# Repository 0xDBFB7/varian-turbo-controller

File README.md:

This is a small, simple half-bridge circuit that commutates 54 volts into 3-phase at 850 Hz, peak power of about 1 kw for a few minutes, for use with the Varian Turbo-V series of turbomolecular pumps. 

> WARNING: This board has only been tested for a few hours. The software does not provide any of the sensing or safety features present in the stock controller. It might blow up your pump, kill your cat, spin the earth around your impeller, etc.
>
> Not that I'm a paragon of best practice in any case, but this seriously isn't an acceptable level of quality. In particular, it was designed to be etched at home, as my normal board house was closed for the holidays.
> I've had one instance where shoot-through blew up one of the MOSFETs. I don't know what would happen if this occurs while the pump is at maximum speed. Adding fuseholders between the legs of the half-bridge - and perhaps between each phase to the pump - would probably be a good idea to prevent catastrophic braking.

There are several other open-source turbomolecular pump controller projects online that are better developed and that might be preferable. In addition, the pumps use a kind of synchronous or induction motor, not a "brushless"-like, so no sensing is needed, only a constant 850 Hz, which is basically just a 3-phase VFD or motor controller. Unfortunately, I wasn't able to find any off-the-shelf system with the required parameters.

The circuit is simple enough to easily be built on perfboard. Schematic and bill of materials are [here](files/controller/assembly). The power MOSFETs are BUK9620, with MIC4604YM-TR half-bridge charge-pump drivers.

The input power was supplied by a MeanWell SE-1000-48 with the voltage trimpot adjusted to ~56V, through a DROK Model 200310 10-75V to 0-60V switching buck converter (Amazon), current limit set to about 8A. 

I highly recommend using such a constant-current regulator, because the power supply is extremely powerful - it's practically an arc flash hazard and will easily start a fire.

The MeanWell supply is probably overkill (very expensive), but a cheaper Amazon 48V supply exploded and I didn't want to tempt fate.

I don't know what terminations the turbopump connector uses; crimp butt connectors worked brilliantly.

## [Original Varian controller manual](references/Varian_V200_controller.pdf)

## [Pump manual](references/Varian_V200_turbo_pump.pdf)

### Things that should be added:

If the back-emf sensing is commutated improperly, -5v or so will be put into the sense ADC pins. The integral protection diodes might be okay with that, but probably not. This is disabled at the moment.

More filtering and decoupling should be added. This pump draws nearly 700 watts on startup - there are some massive transients on the power supply rail.

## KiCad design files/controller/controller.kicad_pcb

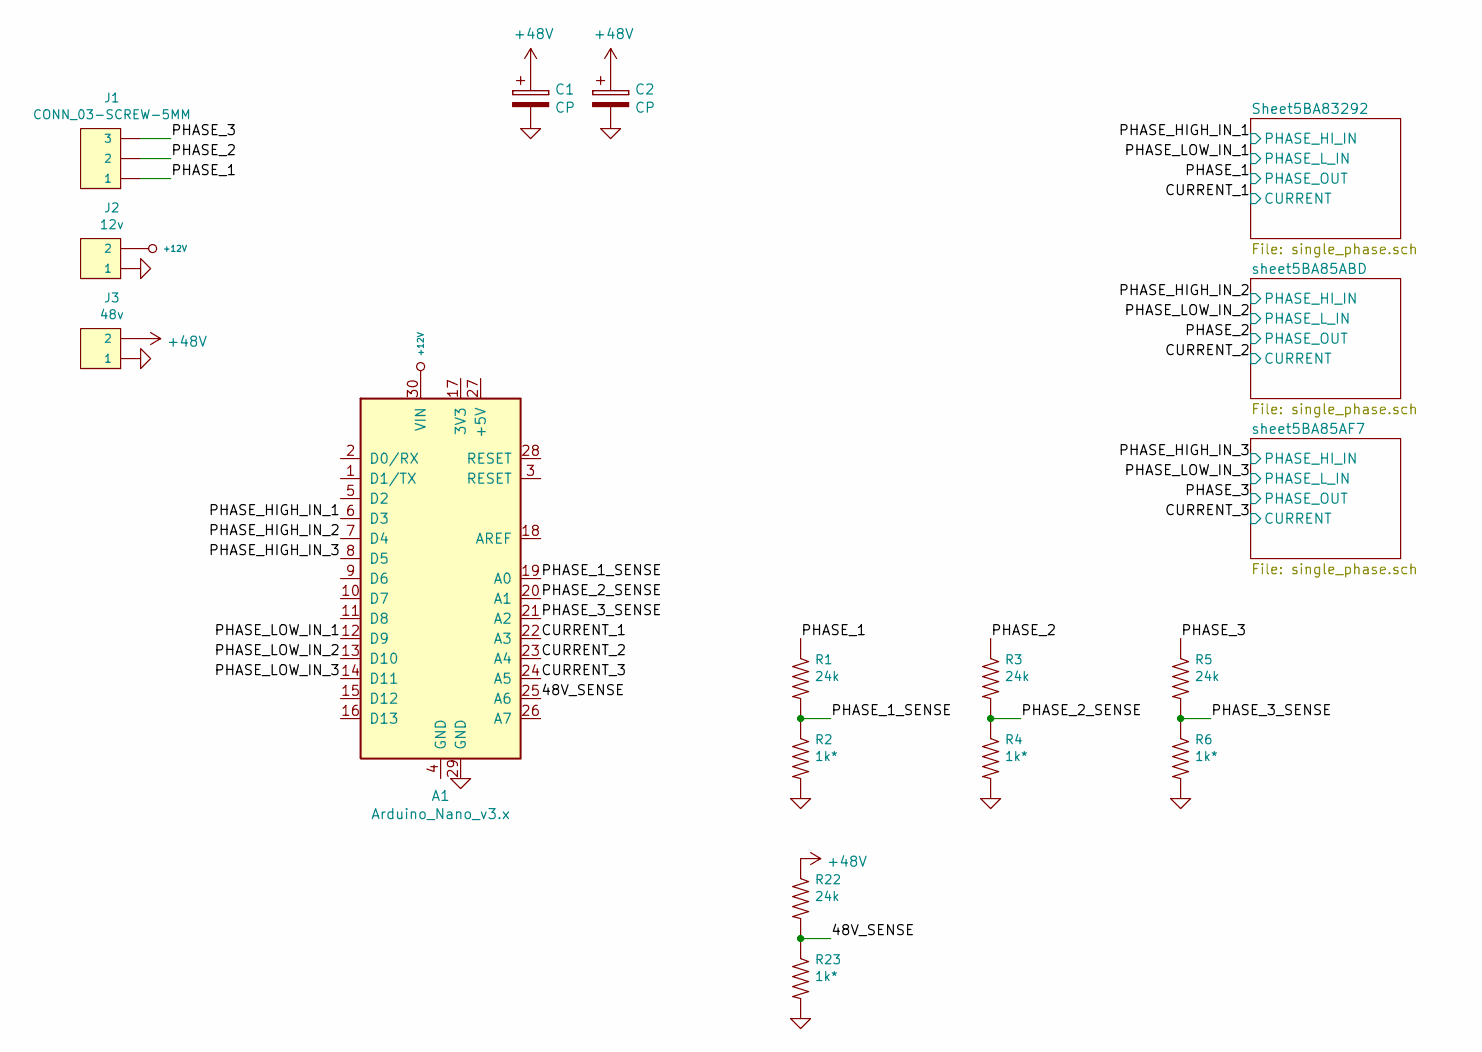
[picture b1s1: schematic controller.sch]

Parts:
A1: Arduino_Nano_v3.x; Arduino_Nano
C1, C2: CP; CP_Radial_D16.0mm_P7.50mm
J1: CONN_03-SCREW-5MM; SCREWTERMINAL-5MM-3
J2: 12v; SCREWTERMINAL-5MM-2
J3: 48v; SCREWTERMINAL-5MM-2
R1, R3, R5, R22: 24k; 0603
R2, R4, R6, R23: 1k*; 0603

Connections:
+12V: A1.30 (VIN), J2.2; also elsewhere on the board
+48V: C1.1, C2.1, J3.2, R22.1; also elsewhere on the board
/48V_SENSE: A1.25 (A6), R22.2, R23.1
/CURRENT_1: A1.22 (A3); also elsewhere on the board
/CURRENT_2: A1.23 (A4); also elsewhere on the board
/CURRENT_3: A1.24 (A5); also elsewhere on the board
/PHASE_1: J1.1, R1.1; also elsewhere on the board
/PHASE_1_SENSE: A1.19 (A0), R1.2, R2.1
/PHASE_2: J1.2, R3.1; also elsewhere on the board
/PHASE_2_SENSE: A1.20 (A1), R3.2, R4.1
/PHASE_3: J1.3, R5.1; also elsewhere on the board
/PHASE_3_SENSE: A1.21 (A2), R5.2, R6.1
/PHASE_HIGH_IN_1: A1.6 (D3); also elsewhere on the board
/PHASE_HIGH_IN_2: A1.7 (D4); also elsewhere on the board
/PHASE_HIGH_IN_3: A1.8 (D5); also elsewhere on the board
/PHASE_LOW_IN_1: A1.12 (D9); also elsewhere on the board
/PHASE_LOW_IN_2: A1.13 (D10); also elsewhere on the board
/PHASE_LOW_IN_3: A1.14 (D11); also elsewhere on the board
GND: A1.29 (GND), C1.2, C2.2, J2.1, J3.1, R2.2, R4.2, R6.2, R23.2; also elsewhere on the board

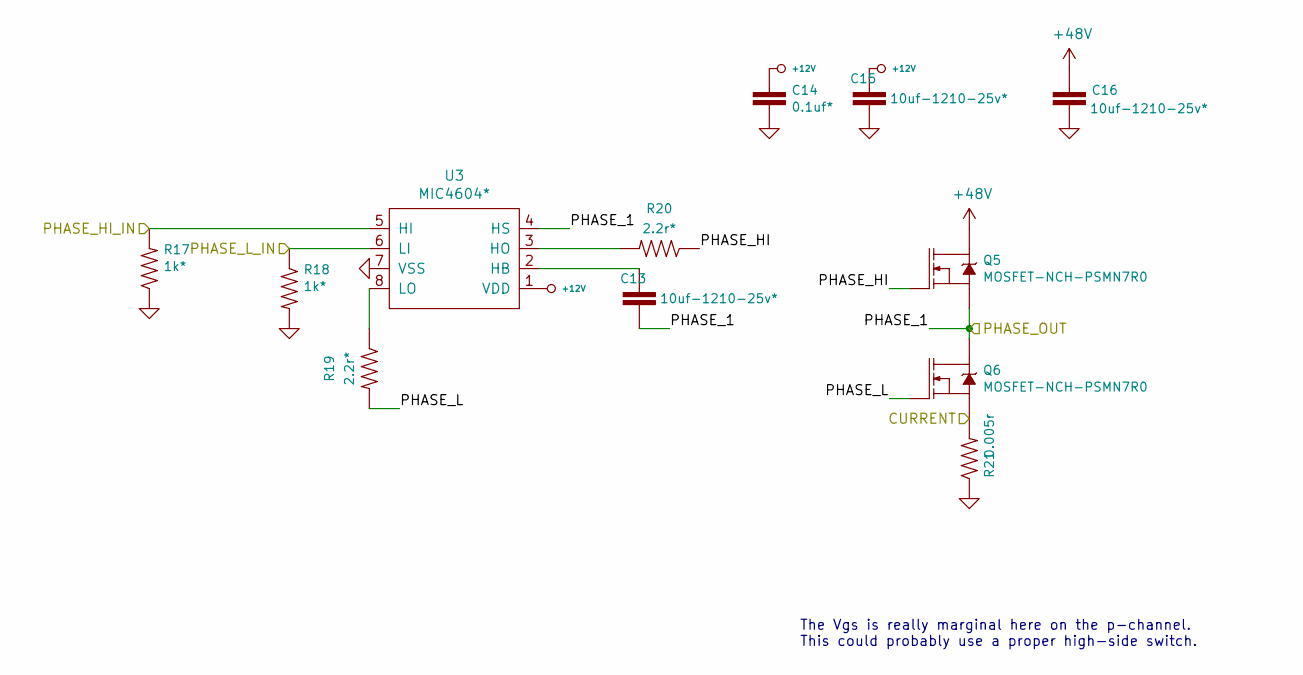
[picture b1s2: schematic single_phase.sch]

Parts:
C5, C7, C8: 10uf-1210-25v*; 1210
C6: 0.1uf*; 0603
Q1, Q2: MOSFET-NCH-PSMN7R0; TO-263_D2PAK
R7, R8: 1k*; 0603
R9, R10: 2.2r*; 0805
R11: 0.005r; 1206
U1: MIC4604*; SOIC-8_3.9x4.9mm_P1.27mm

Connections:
+12V: C6.1, C7.1, U1.1 (VDD); also elsewhere on the board
+48V: C8.1, Q1.2 (D); also elsewhere on the board
/CURRENT_1: Q2.3 (S), R11.2; also elsewhere on the board
/PHASE_1: C5.2, Q1.3 (S), Q2.2 (D), U1.4 (HS); also elsewhere on the board
/PHASE_HIGH_IN_1: R7.2, U1.5 (HI); also elsewhere on the board
/PHASE_LOW_IN_1: R8.1, U1.6 (LI); also elsewhere on the board
/Sheet5BA83292/PHASE_HI: Q1.1 (G), R10.1
/Sheet5BA83292/PHASE_L: Q2.1 (G), R9.2
GND: C6.2, C7.2, C8.2, R7.1, R8.2, R11.1, U1.7 (VSS); also elsewhere on the board
unnamed: C5.1, U1.2 (HB)
unnamed: R9.1, U1.8 (LO)
unnamed: R10.2, U1.3 (HO)

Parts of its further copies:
C9, C11, C12, C13, C15, C16: 10uf-1210-25v*; 1210
C10, C14: 0.1uf*; 0603
Q3, Q4, Q5, Q6: MOSFET-NCH-PSMN7R0; TO-263_D2PAK
R12, R13, R17, R18: 1k*; 0603
R14, R15, R19, R20: 2.2r*; 0805
R16, R21: 0.005r; 1206
U2, U3: MIC4604*; SOIC-8_3.9x4.9mm_P1.27mm

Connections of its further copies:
+12V: C10.1, C11.1, C14.1, C15.1, U2.1 (VDD), U3.1 (VDD); also elsewhere on the board
+48V: C12.1, C16.1, Q3.2 (D), Q5.2 (D); also elsewhere on the board
/CURRENT_2: Q4.3 (S), R16.2; also elsewhere on the board
/CURRENT_3: Q6.3 (S), R21.2; also elsewhere on the board
/PHASE_2: C9.2, Q3.3 (S), Q4.2 (D), U2.4 (HS); also elsewhere on the board
/PHASE_3: C13.2, Q5.3 (S), Q6.2 (D), U3.4 (HS); also elsewhere on the board
/PHASE_HIGH_IN_2: R12.2, U2.5 (HI); also elsewhere on the board
/PHASE_HIGH_IN_3: R17.2, U3.5 (HI); also elsewhere on the board
/PHASE_LOW_IN_2: R13.1, U2.6 (LI); also elsewhere on the board
/PHASE_LOW_IN_3: R18.1, U3.6 (LI); also elsewhere on the board
/sheet5BA85ABD/PHASE_HI: Q3.1 (G), R15.1
/sheet5BA85ABD/PHASE_L: Q4.1 (G), R14.2
/sheet5BA85AF7/PHASE_HI: Q5.1 (G), R20.1
/sheet5BA85AF7/PHASE_L: Q6.1 (G), R19.2
GND: C10.2, C11.2, C12.2, C14.2, C15.2, C16.2, R12.1, R13.2, R16.1, R17.1, R18.2, R21.1, U2.7 (VSS), U3.7 (VSS); also elsewhere on the board
unnamed: C9.1, U2.2 (HB)
unnamed: C13.1, U3.2 (HB)
unnamed: R14.1, U2.8 (LO)
unnamed: R15.2, U2.3 (HO)
unnamed: R19.1, U3.8 (LO)
unnamed: R20.2, U3.3 (HO)

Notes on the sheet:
The Vgs is really marginal here on the p-channel. This could probably use a proper high-side switch.

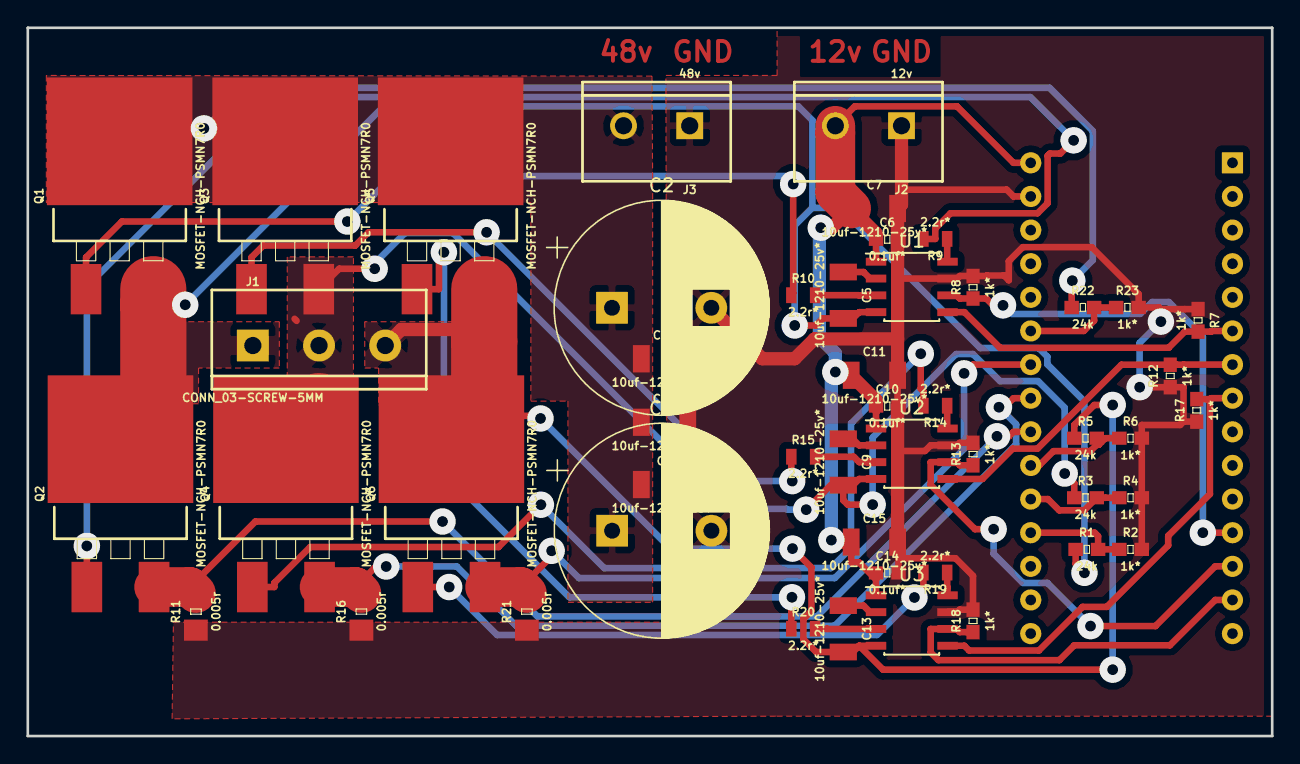
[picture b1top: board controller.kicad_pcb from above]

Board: 2 copper layers, 94.0 x 53.5 mm, 50 parts (1 on the bottom side), 34 nets.

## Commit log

2019-01-15 First!
2019-02-02 Removed some references, added firmware
2020-10-10 assembly
2021-07-27 Cleaned up text
2021-07-27 Fixed folders
2021-07-27 Changed component names
2021-07-27 Renamed file
